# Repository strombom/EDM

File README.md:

# EDM

## Control board
* Stepper motor output.
* Power board control output.
* Buttons for stepper motor up/down and EDM start/stop.
* LCD display 4x20 characters for status.
* Potentiometers for setting voltage, current (not implemented in this revision), on-time and off-time.

## Power board
* Voltage source, low current for initiating spark. Selectable 250 V, 200 V, 150 V or 100 V. Status comparator checks if voltage is above 70 V.
* Current source, for providing current to the spark. Current limited to 10 A, adjustable with potentiometer.
Spark output, has two power transistors to enable the control board to control the voltage and current outputs independently. Has two comparators (5 V and 30 V) to give feedback to the control board, monitoring if a spark has started (breakdown) and to check for short circuit.

## Design files
* [Control Board Schematics](https://github.com/strombom/EDM/raw/master/hardware/edm_control_board/documents/edm_control_board_schematics.pdf)
* [Power Board Schematics](https://github.com/strombom/EDM/raw/master/hardware/edm_power_board/documents/edm_power_board_schematics.pdf)

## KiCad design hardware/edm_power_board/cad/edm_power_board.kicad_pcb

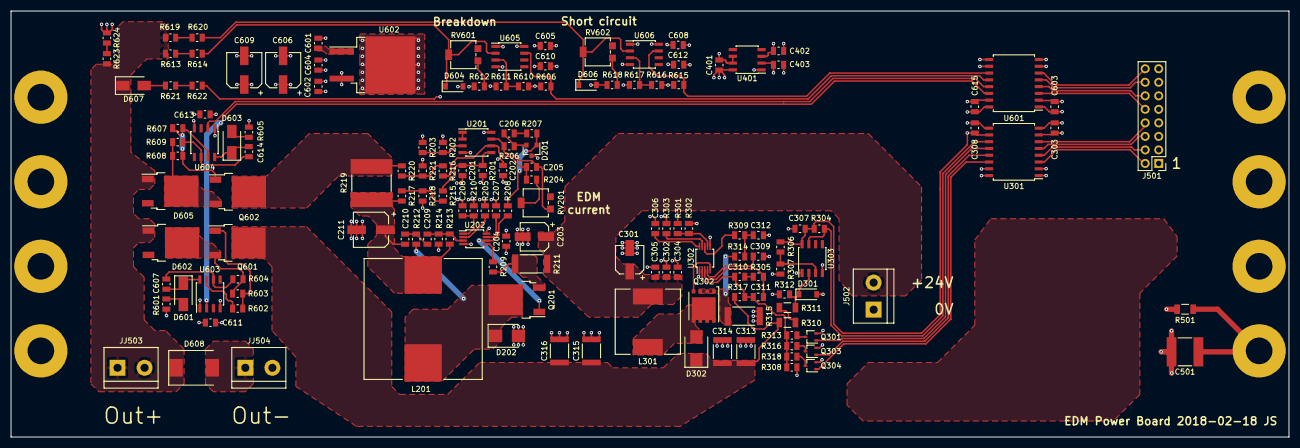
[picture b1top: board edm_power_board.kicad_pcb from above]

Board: 4 copper layers, 240.0 x 80.0 mm, 158 parts (0 on the bottom side), 89 nets.

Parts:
C201, C205: 220p; R_0805_2012Metric
C202, C204, C209, C303, C307, C308, C402, C602, C603, C605, C608, C610, C611, C612, C613, C615: 100n; C_0805_2012Metric
C203, C301: 22u; CP_Elec_5x5.3
C206, C306: 10n; C_0805_2012Metric
C207, C607, C614: 470n; C_0805_2012Metric
C208, C312: 1n; C_0805_2012Metric
C210: 3n3; C_0805_2012Metric
C211, C606, C609: 10u; CP_Elec_6.3x5.3
C302, C304, C305, C309, C403, C604: 1u; C_0805_2012Metric
C310: 120n; C_0805_2012Metric
C311: 560p; C_0805_2012Metric
C313, C314, C315, C316: 470n; C_1812_4532Metric
C401, C601: 330n; C_0805_2012Metric
C501: 1800p; C_2220_5650Metric
D201: TL431AIDBZR; SOT-23
D202, D302: S2JTR; D_SMB
D301, D604, D606: 4V7; D_SOD-123
D601, D603, D607: RS1MTR; D_SMA
D602, D605: VS-15EWL06FNTR-M3; TO-252-2
D608: 1.5SMC400CA; D_SMC
J501: Conn_02x08_Odd_Even; PinHeader_2x08_P2.54mm_Vertical
J502: Conn_01x02; TerminalBlock_bornier-2_P5.08mm
JJ503, JJ504: Conn_01x02; TerminalBlock_bornier-2_P5.08mm
L201: 6u8; L_Wuerth_HCI-2212
L301: 1m; L_Pulse_PA4320
MK501, MK502, MK503, MK504, MK507, MK508, MK509, MK510: Mounting_Hole_PAD; MountingHole_5mm_Pad
Q201: SUD19P06-60; TO-252-2
Q301, Q303, Q304: BSS214NW; SOT-323_SC-70
Q302: BSC13DN30NSFD; TDSON-8-1
Q601: IPD50R3K0CE; TO-252-2
Q602: IPD50R380CE; TO-252-2
R201, R202, R203, R207, R301, R306, R610, R616, R617: 27k; R_0805_2012Metric
R204, R208, R603, R608: 4k7; R_0805_2012Metric
R205: 243k; R_0805_2012Metric
R206: 10R; R_0805_2012Metric
R209: 100R; R_0805_2012Metric
R210: 6k34; R_0805_2012Metric
R211: 10m; R_2512_6332Metric
R212: 47k; R_0805_2012Metric
R213: 15k; R_0805_2012Metric
R214, R215, R216, R217, R218, R220, R221: 1k; R_0805_2012Metric
R219: 20m; R_Stackpole_CSSH2728_4-100m
R302: 2k2; R_0805_2012Metric
R303, R307, R611: 84k5; R_0805_2012Metric
R304, R606, R612, R615, R618, R621, R622: 21k; R_0805_2012Metric
R305: 3k; R_0805_2012Metric
R308, R316: 26k1; R_0805_2012Metric
R309: 10k5; R_0805_2012Metric
R310, R311: 93k1; R_1206_3216Metric
R312: 10k; R_0805_2012Metric
R313: 52k3; R_0805_2012Metric
R314: 102R; R_0805_2012Metric
R315: 150m; R_2512_6332Metric
R317: 2M1; R_0805_2012Metric
R318: 18k; R_0805_2012Metric
R501: 1M; R_1206_3216Metric
R601, R604, R605, R609: 4R99; R_0805_2012Metric
R602, R607: 47R; R_0805_2012Metric
R613, R614, R619, R620, R623, R624: 187k; R_0805_2012Metric
RV201: 50k; Potentiometer_Bourns_3314G_Horizontal
RV601: 100k; Potentiometer_Bourns_3314G_Horizontal
RV602: 500k; Potentiometer_Bourns_3314G_Horizontal
U201: LM358; SOIC-8_3.9x4.9mm_P1.27mm
U202: LM25085MM; MSOP-8_3x3mm_P0.65mm
U301: Si8641BB-B-IS; SOIC-16W_7.5x10.3mm_P1.27mm
U302: LM5022MM; MSOP-10_3x3mm_P0.5mm
U303, U605, U606: LM311; SOIC-8_3.9x4.9mm_P1.27mm
U401: L78L05_SO8; SOIC-8_3.9x4.9mm_P1.27mm
U601: Si8642BB-B-IS; SOIC-16W_7.5x10.3mm_P1.27mm
U602: L7815; TO-263-2
U603, U604: FAN7371; SOIC-8_3.9x4.9mm_P1.27mm

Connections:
+3V3: C303.1, C603.1, J501.1, U301.1, U301.7, U601.1, U601.7
+5V: C307.1, C308.1, C402.1, C403.1, C605.1, C608.1, C610.1, C612.1, C615.1, R304.1, R306.1, R606.2, R610.2, R615.2, R616.2, R622.2, U301.10, U301.16, U303.8, U401.1, U601.10, U601.16, U605.8, U606.8
+15V: C602.1, C604.1, C606.1, C609.1, C611.1, C613.1, R601.2, R605.2, U602.3, U603.1, U604.1
+24V: C202.1, C203.1, C204.1, C207.1, C208.1, C301.1, C302.1, C304.1, C305.1, C401.1, J502.2, L301.1, R202.1, R205.1, R210.1, R211.1, R301.1, U201.8, U202.8, U302.1, U401.8
/Connectors/Breakdown: J501.16, U601.6
/Connectors/Output_20V_Enable: J501.12, U601.4
/Connectors/Output_250V_Enable: J501.10, U601.3
/Connectors/Shield: C501.1, MK501.1, MK502.1, MK503.1, MK504.1, MK507.1, MK508.1, MK509.1, MK510.1, R501.1
/Connectors/Short_Circuit: J501.14, U601.5
/Connectors/Spark_Output: D602.1, D605.1, D607.1, D608.1, JJ503.1, JJ503.2, R613.2, R619.2, R623.2
/Connectors/Spark_Voltage_0: J501.2, U301.3
/Connectors/Spark_Voltage_1: J501.4, U301.4
/Connectors/Spark_Voltage_2: J501.6, U301.5
/Connectors/Spark_Voltage_Status: J501.8, U301.6
/Current Source/+20V: Q602.2, R219.1, R220.1
/Current Source/CS_1: C205.1, R206.2, RV201.3, U201.7
/Current Source/CS_1+: R216.1, R220.2, R221.1
/Current Source/CS_1-: R215.1, R217.2, R218.1
/Current Source/CS_2: C206.2, D201.2, R206.1
/Current Source/CS_2+: C205.2, R204.2, R216.2, U201.6
/Current Source/CS_2-: C201.1, R201.1, R215.2, U201.5
/Current Source/CS_3: C206.1, R207.2
/Current Source/CS_4: D201.1, R207.1, R208.2
/Current Source/CS_5: R204.1, RV201.2
/Current Source/CS_ADJ: C208.2, R210.2, U202.1
/Current Source/CS_FB: C209.2, R213.2, R214.1, U202.3
/Current Source/CS_ISEN: R209.2, U202.5
/Current Source/CS_NC1: R202.2, R203.1, U201.3
/Current Source/CS_NC2: U201.1, U201.2
/Current Source/CS_OUT: C210.1, C211.1, L201.2, R213.1, R217.1, R219.2
/Current Source/CS_PGATE: Q201.1, R208.1, U202.6
/Current Source/CS_QD: D202.1, L201.1, Q201.2, R212.2
/Current Source/CS_QD1: C209.1, C210.2, R212.1
/Current Source/CS_QS: Q201.3, R209.1, R211.2
/Current Source/CS_RT: R205.2, U202.2
/Current Source/CS_VCC: C207.2, U202.7
/Spark Output/+20V_Out: D605.2, Q602.3, R608.1, R609.1
/Spark Output/+24V: C601.1, U602.1
/Spark Output/+250V: C313.1, C314.1, C315.1, C316.1, D302.1, Q601.2, R310.1, R317.1
/Spark Output/+250V_Out: D602.2, Q601.3, R603.1, R604.1
/Spark Output/HV_ENA: R602.2, U603.7
/Spark Output/HV_ENB: Q601.1, R602.1, R603.2
/Spark Output/HV_VB: C607.1, D601.1, U603.8
/Spark Output/HV_VS: C607.2, R604.2, U603.6
/Spark Output/LV_ENA: R607.2, U604.7
/Spark Output/LV_ENB: Q602.1, R607.1, R608.2
/Spark Output/LV_VB: C614.1, D603.1, U604.8
/Spark Output/LV_VS: C614.2, R609.2, U604.6
/Spark Voltage Source/VS_COMP: C311.2, R305.2, U302.3
/Spark Voltage Source/VS_CS: R309.2, U302.8
/Spark Voltage Source/VS_CS2: C312.1, R309.1, R314.2
/Spark Voltage Source/VS_FB: C310.1, C311.1, R308.1, R313.1, R316.1, R317.2, R318.1, U302.2
/Spark Voltage Source/VS_OUT: Q302.4, U302.5
/Spark Voltage Source/VS_QD: D302.2, L301.2, Q302.5
/Spark Voltage Source/VS_QS: Q302.1, Q302.2, Q302.3, R314.1, R315.1
/Spark Voltage Source/VS_RT: R303.1, U302.9
/Spark Voltage Source/VS_UVLO: R301.2, R302.1, U302.7
/Spark Voltage Source/VS_VCC: C309.1, U302.4
GND: C303.2, C603.2, J501.3, J501.5, J501.7, J501.9, J501.11, J501.13, J501.15, U301.2, U301.8, U601.2, U601.8
GNDPWR: C201.2, C202.2, C203.2, C204.2, C211.2, C301.2, C302.2, C304.2, C305.2, C306.2, C307.2, C308.2, C309.2, C312.2, C313.2, C314.2, C315.2, C316.2, C401.2, C402.2, C403.2, C501.2, C601.2, C602.2, C604.2, C605.2, C606.2, C608.2, C609.2, C610.2, C611.2, C612.2, C613.2, C615.2, D201.3, D202.2, D301.2, D604.2, D606.2, D608.2, J502.1, JJ504.1, JJ504.2, Q301.2, Q303.2, Q304.2, R201.2, R203.2, R214.2, R218.2, R221.2, R302.2, R303.2, R307.2, R308.2, R312.2, R315.2, R501.2, R611.1, R612.1, R617.1, R618.1, R624.1, U201.4, U202.4, U301.9, U301.15, U302.6, U303.1, U303.4, U401.2, U401.3, U401.6, U401.7, U601.9, U601.15, U602.2, U603.4, U604.4, U605.1, U605.4, U606.1, U606.4
unnamed: C306.1, U302.10
unnamed: C310.2, R305.1
unnamed: D301.1, R311.2, R312.1, U303.2
unnamed: D601.2, R601.1
unnamed: D603.2, R605.1
unnamed: D604.1, R614.1, RV601.2, U605.2
unnamed: D606.1, R620.1, RV602.2, U606.2
unnamed: D607.2, R621.1
unnamed: Q301.1, U301.12
unnamed: Q301.3, R313.2
unnamed: Q303.1, U301.13
unnamed: Q303.3, R316.2
unnamed: Q304.1, U301.14
unnamed: Q304.3, R318.2
unnamed: R304.2, U301.11, U303.7
unnamed: R306.2, R307.1, U303.3
unnamed: R310.2, R311.1
unnamed: R606.1, U601.12, U605.7
unnamed: R610.1, R611.2, U605.3
unnamed: R612.2, RV601.3
unnamed: R613.1, R614.2
unnamed: R615.1, U601.11, U606.7
unnamed: R616.1, R617.2, U606.3
unnamed: R618.2, RV602.3
unnamed: R619.1, R620.2
unnamed: R621.2, R622.1
unnamed: R623.1, R624.2
unnamed: U601.13, U604.2
unnamed: U601.14, U603.2

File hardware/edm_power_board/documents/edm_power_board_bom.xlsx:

Ref | Qnty | Value | Digikey | Footprint
C201, C205 | 2 | 220p | 311-1115-1-ND | Resistor_SMD:R_0805_2012Metric
C203, C301 | 2 | 22u | PCE4240CT-ND | Capacitor_SMD:CP_Elec_5x5.3
C204, C209, C202, C308, C303, C307, C402, C603, C605, C608, C610, C612, C602, C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 | 16 | 100n | 445-1418-1-ND | Capacitor_SMD:C_0805_2012Metric
C206, C306 | 2 | 10n | 490-1664-1-ND | Capacitor_SMD:C_0805_2012Metric
C207, C607, C614 | 3 | 470n | 1276-1074-1-ND | Capacitor_SMD:C_0805_2012Metric
C208, C312 | 2 | 1n | 399-1147-1-ND | Capacitor_SMD:C_0805_2012Metric
C210 | 1 | 3n3 | 311-1131-1-ND | Capacitor_SMD:C_0805_2012Metric
C211, C606, C609 | 3 | 10u | PCE4209CT-ND | Capacitor_SMD:CP_Elec_6.3x5.3
C309, C305, C304, C302, C403, C604 | 6 | 1u | 587-2910-1-ND | Capacitor_SMD:C_0805_2012Metric
C310 | 1 | 120n | 1276-6518-1-ND | Capacitor_SMD:C_0805_2012Metric
C311 | 1 | 560p | 399-3492-1-ND | Capacitor_SMD:C_0805_2012Metric
C313, C314, C315, C316 | 4 | 470n | 445-13461-1-ND | Capacitor_SMD:C_1812_4532Metric
C401, C601 | 2 | 330n | 1276-6813-1-ND | Capacitor_SMD:C_0805_2012Metric
C501 | 1 | 1800p | 490-3479-1-ND | Capacitor_SMD:C_2220_5650Metric
D201 | 1 | TL431AIDBZR | 296-17329-1-ND | Package_TO_SOT_SMD:SOT-23
D202, D302 | 2 | S2JTR | 1655-1739-1-ND | Diode_SMD:D_SMB
D301, D604, D606 | 3 | 4V7 | BZT52C4V7-13FDICT-ND | Diode_SMD:D_SOD-123
D601, D603, D607 | 3 | RS1MTR | 1655-1501-1-ND | Diode_SMD:D_SMA
D602, D605 | 2 | VS-15EWL06FNTR-M3 | VS-15EWL06FNTR-M3CT-ND | Package_TO_SOT_SMD:TO-252-2
D608 | 1 | 1.5SMC400CA | 1.5SMC400CACT-ND | Diode_SMD:D_SMC
J501 | 1 | Conn_02x08_Odd_Even | ED10523-ND | Connector_PinHeader_2.54mm:PinHeader_2x08_P2.54mm_Vertical
J502, JJ503, JJ504 | 3 | Conn_01x02 | ED1609-ND | TerminalBlock:TerminalBlock_bornier-2_P5.08mm
L201 | 1 | 6u8 | 732-4233-1-ND | Inductor_SMD:L_Wuerth_HCI-2212
L301 | 1 | 1m | 553-3686-1-ND | Inductor_SMD:L_Pulse_PA4320
Q201 | 1 | SUD19P06-60 | SUD19P06-60-GE3CT-ND | Package_TO_SOT_SMD:TO-252-2
Q301, Q303, Q304 | 3 | BSS214NW | BSS214NWH6327XTSA1CT-ND | Package_TO_SOT_SMD:SOT-323_SC-70
Q302 | 1 | BSC13DN30NSFD | BSC13DN30NSFDATMA1CT-ND | Package_TO_SOT_SMD:TDSON-8-1
Q601 | 1 | IPD50R3K0CE | IPD50R3K0CEAUMA1CT-ND | Package_TO_SOT_SMD:TO-252-2
Q602 | 1 | IPD50R380CE | IPD50R380CEAUMA1CT-ND | Package_TO_SOT_SMD:TO-252-2
R201, R207, R202, R203, R301, R306, R610, R616, R617 | 9 | 27k | 311-27.0KCRCT-ND | Resistor_SMD:R_0805_2012Metric
R204, R208, R603, R608 | 4 | 4k7 | 311-4.70KCRCT-ND | Resistor_SMD:R_0805_2012Metric
R205 | 1 | 243k | YAG1838CT-ND | Resistor_SMD:R_0805_2012Metric
R206 | 1 | 10R | 311-10.0CRCT-ND | Resistor_SMD:R_0805_2012Metric
R209 | 1 | 100R | 311-100CRCT-ND | Resistor_SMD:R_0805_2012Metric
R210 | 1 | 6k34 | 311-6.34KCRCT-ND | Resistor_SMD:R_0805_2012Metric
R211 | 1 | 10m | CRA2512-FZ-R010ELFCT-ND | Resistor_SMD:R_2512_6332Metric
R212 | 1 | 47k | 311-47.0KCRCT-ND | Resistor_SMD:R_0805_2012Metric
R213 | 1 | 15k | 311-15.0KCRCT-ND | Resistor_SMD:R_0805_2012Metric
R214, R217, R220, R218, R221, R215, R216 | 7 | 1k | 311-1.00KCRCT-ND | Resistor_SMD:R_0805_2012Metric
R219 | 1 | 20m | CSSH2728FT20L0CT-ND | Resistor_SMD:R_Stackpole_CSSH2728_4-100m
R302 | 1 | 2k2 | 311-2.20KCRCT-ND | Resistor_SMD:R_0805_2012Metric
R304, R606, R612, R615, R618, R621, R622 | 7 | 21k | 311-21.0KCRCT-ND | Resistor_SMD:R_0805_2012Metric
R305 | 1 | 3k | 311-3.00KCRCT-ND | Resistor_SMD:R_0805_2012Metric
R307, R303, R611 | 3 | 84k5 | 311-84.5KCRCT-ND | Resistor_SMD:R_0805_2012Metric
R308, R316 | 2 | 26k1 | 311-26.1KCRCT-ND | Resistor_SMD:R_0805_2012Metric
R309 | 1 | 10k5 | 311-10.5KCRCT-ND | Resistor_SMD:R_0805_2012Metric
R311, R310 | 2 | 93k1 | 311-93.1KCRCT-ND | Resistor_SMD:R_1206_3216Metric
R312 | 1 | 10k | 311-10.0KCRCT-ND | Resistor_SMD:R_0805_2012Metric
R313 | 1 | 52k3 | 311-52.3KCRCT-ND | Resistor_SMD:R_0805_2012Metric
R314 | 1 | 102R | 311-102CRCT-ND | Resistor_SMD:R_0805_2012Metric
R315 | 1 | 150m | 311-0.15TCT-ND | Resistor_SMD:R_2512_6332Metric
R317 | 1 | 2M1 | 311-2.10MCRCT-ND | Resistor_SMD:R_0805_2012Metric
R318 | 1 | 18k | 311-18.0KCRCT-ND | Resistor_SMD:R_0805_2012Metric
R501 | 1 | 1M | 311-1.00MFRCT-ND | Resistor_SMD:R_1206_3216Metric
R601, R604, R605, R609 | 4 | 4R99 | 311-4.99CRCT-ND | Resistor_SMD:R_0805_2012Metric
R602, R607 | 2 | 47R | 311-47.0CRCT-ND | Resistor_SMD:R_0805_2012Metric
R613, R614, R619, R620, R623, R624 | 6 | 187k | 311-187KCRCT-ND | Resistor_SMD:R_0805_2012Metric
RV201 | 1 | 50k | 3314G-503ECT-ND | Potentiometer_SMD:Potentiometer_Bourns_3314G_Horizontal
RV601 | 1 | 100k | 3314G-104ECT-ND | Potentiometer_SMD:Potentiometer_Bourns_3314G_Horizontal
RV602 | 1 | 500k | 3314G-504ECT-ND | Potentiometer_SMD:Potentiometer_Bourns_3314G_Horizontal
U201 | 1 | LM358 | LM358F-GE2CT-ND | Package_SO:SOIC-8_3.9x4.9mm_P1.27mm
U202 | 1 | LM25085MM | LM25085MM/NOPBCT-ND | Package_SO:MSOP-8_3x3mm_P0.65mm
U301 | 1 | Si8641BB-B-IS | SI8641BB-B-IS-ND | Package_SO:SOIC-16W_7.5x10.3mm_P1.27mm
U302 | 1 | LM5022MM | LM5022MM/NOPBCT-ND | Package_SO:MSOP-10_3x3mm_P0.5mm
U303, U605, U606 | 3 | LM311 | LM311MX/NOPBCT-ND | Package_SO:SOIC-8_3.9x4.9mm_P1.27mm
U401 | 1 | L78L05_SO8 | 497-1182-1-ND | Package_SO:SOIC-8_3.9x4.9mm_P1.27mm
U601 | 1 | Si8642BB-B-IS | SI8642BB-B-IS-ND | Package_SO:SOIC-16W_7.5x10.3mm_P1.27mm
U602 | 1 | L7815 | 497-1179-1-ND | Package_TO_SOT_SMD:TO-263-2
U603, U604 | 2 | FAN7171 | FAN7171MX-F085FSCT-ND | Package_SO:SOIC-8_3.9x4.9mm_P1.27mm

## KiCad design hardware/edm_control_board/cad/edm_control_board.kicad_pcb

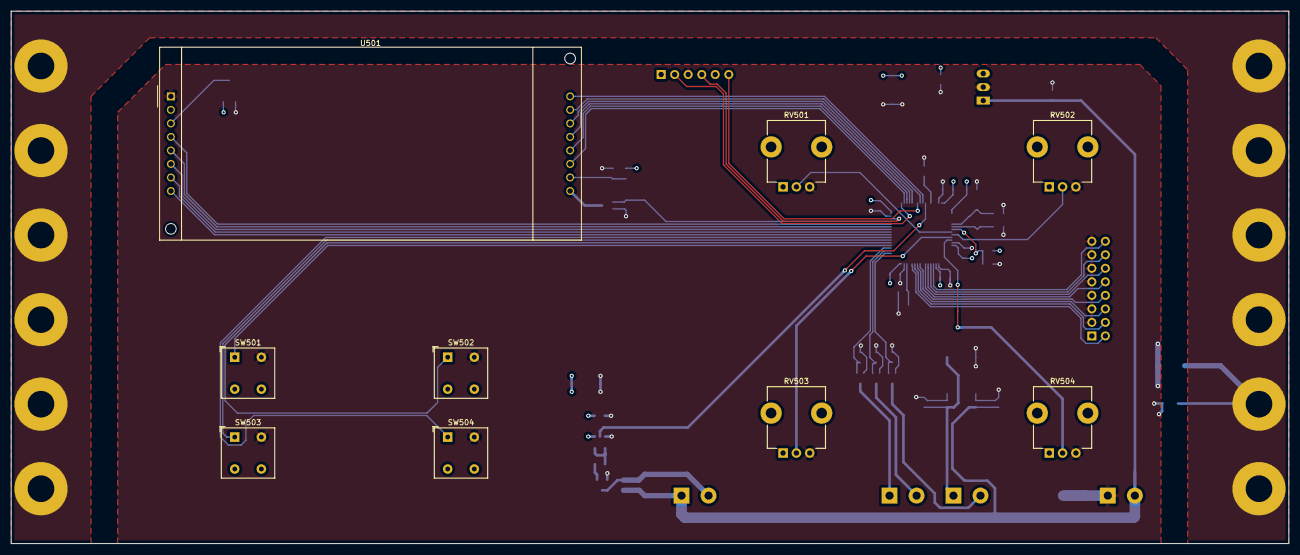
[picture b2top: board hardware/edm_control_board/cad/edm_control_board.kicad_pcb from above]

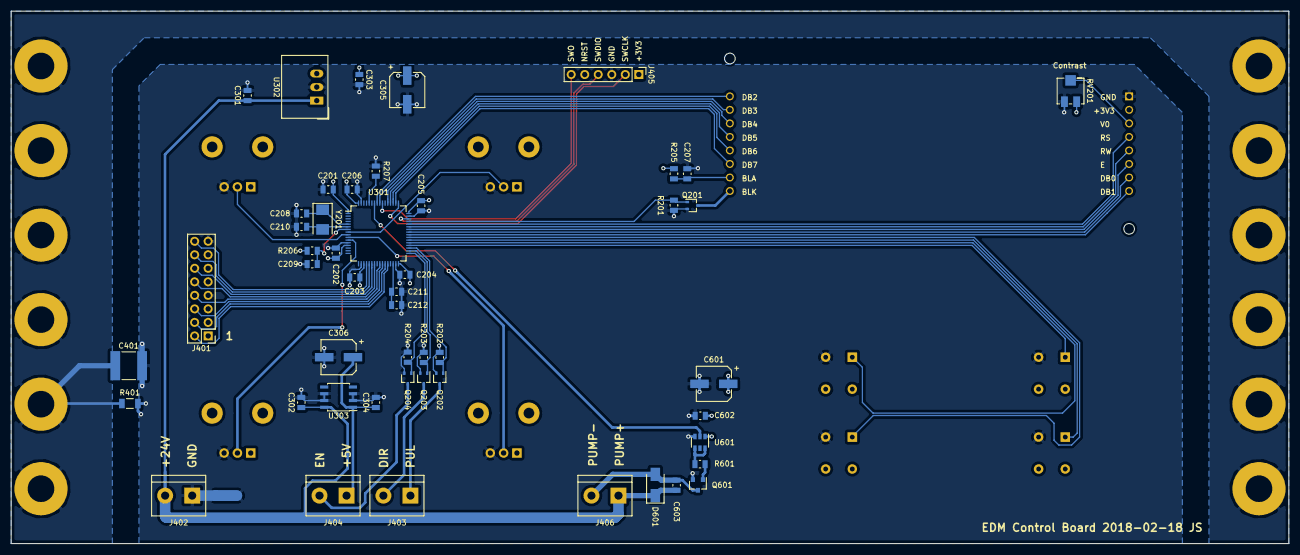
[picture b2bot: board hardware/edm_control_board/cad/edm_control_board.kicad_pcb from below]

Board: 4 copper layers, 240.0 x 100.0 mm, 71 parts (50 on the bottom side), 54 nets.

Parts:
C201, C202, C203, C204, C205, C206, C209, C303, C304, C602: 100n; C_0805_2012Metric
C207: 1u; C_0805_2012Metric
C208, C210: 12p; C_0805_2012Metric
C211, C212: 2u2; C_0805_2012Metric
C301, C302: 330n; C_0805_2012Metric
C305, C306, C601: 10u; CP_Elec_6.3x5.3
C401: 1800p; C_2220_5650Metric
C603: 1n; C_0805_2012Metric
D601: CDBA140-G; D_SMA
J401: Conn_02x08_Odd_Even; PinHeader_2x08_P2.54mm_Vertical
J402, J403, J404, J406: Conn_01x02; TerminalBlock_bornier-2_P5.08mm
J405: Conn_01x06; PinHeader_1x06_P2.54mm_Vertical
MK501, MK502, MK503, MK504, MK505, MK506, MK507, MK508, MK509, MK510, MK511, MK512: Mounting_Hole_PAD; MountingHole_5mm_Pad
NT301: Net-Tie_2; NetTie-2_SMD_Pad2.0mm
Q201, Q202, Q203, Q204: BSS214NW; SOT-323_SC-70
Q601: DMN3404L-7; SOT-23
R201, R202, R203, R204, R206, R207: 27k; R_0805_2012Metric
R205: 20R; R_0805_2012Metric
R401: 1M; R_1206_3216Metric
R601: 4R99; R_0805_2012Metric
RV201: 20k; Potentiometer_Bourns_3214J_Horizontal
RV501, RV502, RV503, RV504: POT; Potentiometer_TT_P0915N
SW501, SW502, SW503, SW504: SW_Push; SW_PUSH_CK_PVA1
U301: STM32F722RETx; LQFP-64_10x10mm_P0.5mm
U302: R-78E3.3-1.0; Converter_DCDC_RECOM_R-78E-0.5_THT
U303: L78L05_SO8; SOIC-8_3.9x4.9mm_P1.27mm
U501: NHD-0420H1Z
U601: ZXGD3009E6; SOT-23-6
Y201: 25M; Crystal_SMD_5032-2Pin_5.0x3.2mm

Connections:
+3V3: C201.1, C202.1, C203.1, C204.1, C205.1, C206.1, C303.1, C305.1, C601.1, C602.1, J401.1, J405.1, R205.2, R206.2, RV201.1, RV501.1, RV502.1, RV503.1, RV504.1, U301.1, U301.13, U301.19, U301.32, U301.48, U301.64, U302.3, U501.2, U601.1
+5V: C304.1, C306.1, J404.1, U303.1
+24V: C301.1, C302.1, C603.1, D601.1, J402.2, J406.1, U302.1, U303.8
/Connectors/Breakdown: J401.16, U301.20
/Connectors/Output_20V_Enable: J401.12, U301.22
/Connectors/Output_250V_Enable: J401.10, U301.23
/Connectors/SWCLK: J405.2, U301.49
/Connectors/SWDIO: J405.4, U301.46
/Connectors/SWO: J405.6, U301.55
/Connectors/Shield: C401.1, MK501.1, MK502.1, MK503.1, MK504.1, MK505.1, MK506.1, MK507.1, MK508.1, MK509.1, MK510.1, MK511.1, MK512.1, R401.1
/Connectors/Short_Circuit: J401.14, U301.21
/Connectors/Spark_Voltage_0: J401.2, U301.28
/Connectors/Spark_Voltage_1: J401.4, U301.27
/Connectors/Spark_Voltage_2: J401.6, U301.26
/Connectors/Spark_Voltage_Status: J401.8, U301.25
/Connectors/Stepper_DIR: J403.2, Q203.3
/Connectors/Stepper_EN: J404.2, Q204.3
/Connectors/Stepper_PUL: J403.1, Q202.3
/Connectors/Water_Pump_NEG: C603.2, D601.2, J406.2, Q601.3
/Controller/LCD_A: C207.1, R205.1, U501.15
/Controller/LCD_DB0: U301.41, U501.7
/Controller/LCD_DB1: U301.40, U501.8
/Controller/LCD_DB2: U301.57, U501.9
/Controller/LCD_DB3: U301.56, U501.10
/Controller/LCD_DB4: U301.53, U501.11
/Controller/LCD_DB5: U301.52, U501.12
/Controller/LCD_DB6: U301.51, U501.13
/Controller/LCD_DB7: U301.50, U501.14
/Controller/LCD_E: U301.42, U501.6
/Controller/LCD_K: Q201.3, U501.16
/Controller/LCD_RS: U301.44, U501.4
/Controller/LCD_RW: U301.43, U501.5
/Controller/LCD_V0: RV201.2, U501.3
/Controller/POT_1: RV501.2, U301.8
/Controller/POT_2: RV502.2, U301.9
/Controller/POT_3: RV503.2, U301.10
/Controller/POT_4: RV504.2, U301.11
/Controller/SW_1: SW501.1, U301.36
/Controller/SW_2: SW502.1, U301.37
/Controller/SW_3: SW503.1, U301.38
/Controller/SW_4: SW504.1, U301.39
/Controller/Water_Pump_PWM: U301.58, U601.2
GND: C201.2, C202.2, C203.2, C204.2, C205.2, C206.2, C207.2, C208.2, C209.2, C210.2, C211.2, C212.2, C301.2, C302.2, C303.2, C304.2, C305.2, C306.2, C401.2, C601.2, C602.2, J401.3, J401.5, J401.7, J401.9, J401.11, J401.13, J401.15, J402.1, J405.3, NT301.1, NT301.2, Q201.2, Q202.2, Q203.2, Q204.2, Q601.2, R201.2, R202.2, R203.2, R204.2, R207.2, R401.2, RV201.3, RV501.3, RV502.3, RV503.3, RV504.3, SW501.2, SW502.2, SW503.2, SW504.2, U301.12, U301.18, U301.31, U301.47, U301.63, U302.2, U303.2, U303.3, U303.6, U303.7, U501.1, U601.3
unnamed: C208.1, U301.5, Y201.1
unnamed: C209.1, R206.1, U301.7
unnamed: C210.1, U301.6, Y201.2
unnamed: C211.1, C212.1, U301.30
unnamed: Q201.1, R201.1, U301.45
unnamed: Q202.1, R202.1, U301.35
unnamed: Q203.1, R203.1, U301.34
unnamed: Q204.1, R204.1, U301.33
unnamed: Q601.1, R601.1
unnamed: R207.1, U301.60
unnamed: R601.2, U601.4, U601.6

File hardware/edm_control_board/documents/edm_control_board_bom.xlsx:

Ref | Qnty | Value | Digikey | Footprint
C201, C202, C203, C204, C205, C209, C206, C303, C304, C602 | 10 | 100n | 445-1418-1-ND | Capacitor_SMD:C_0805_2012Metric
C207 | 1 | 1u | 587-2910-1-ND | Capacitor_SMD:C_0805_2012Metric
C210, C208 | 2 | 12p | 311-1100-1-ND | Capacitor_SMD:C_0805_2012Metric
C212, C211 | 2 | 2u2 | 311-3425-1-ND | Capacitor_SMD:C_0805_2012Metric
C301, C302 | 2 | 330n | 1276-6813-1-ND | Capacitor_SMD:C_0805_2012Metric
C305, C306, C601 | 3 | 10u | PCE4209CT-ND | Capacitor_SMD:CP_Elec_6.3x5.3
C401 | 1 | 1800p | 490-3479-1-ND | Capacitor_SMD:C_2220_5650Metric
C603 | 1 | 1n | 311-1469-1-ND | Capacitor_SMD:C_0805_2012Metric
D601 | 1 | CDBA140-G | 641-1015-1-ND | Diode_SMD:D_SMA
J401 | 1 | Conn_02x08_Odd_Even | ED10523-ND | Connector_PinHeader_2.54mm:PinHeader_2x08_P2.54mm_Vertical
J402, J404, J403, J406 | 4 | Conn_01x02 | ED1609-ND | TerminalBlock:TerminalBlock_bornier-2_P5.08mm
J405 | 1 | Conn_01x06 | 952-2270-ND | Connector_PinHeader_2.54mm:PinHeader_1x06_P2.54mm_Vertical
Q202, Q203, Q204, Q201 | 4 | BSS214NW | BSS214NWH6327XTSA1 | Package_TO_SOT_SMD:SOT-323_SC-70
Q601 | 1 | DMN3404L-7 | DMN3404LDICT-ND | Package_TO_SOT_SMD:SOT-23
R202, R203, R204, R201, R207, R206 | 6 | 27k | 311-27.0KCRCT-ND | Resistor_SMD:R_0805_2012Metric
R205 | 1 | 20R | 311-20.0CRCT-ND | Resistor_SMD:R_0805_2012Metric
R401 | 1 | 1M | 311-1.00MFRCT-ND | Resistor_SMD:R_1206_3216Metric
R601 | 1 | 4R99 | 311-4.99CRCT-ND | Resistor_SMD:R_0805_2012Metric
RV201 | 1 | 20k | 3214J-203ECT-ND | Potentiometer_SMD:Potentiometer_Bourns_3214J_Horizontal
RV501, RV503, RV502, RV504 | 4 | POT | 987-1278-ND | Potentiometer_THT:Potentiometer_TT_P0915N
SW501, SW503, SW502, SW504 | 4 | SW_Push | 401-1137-ND | Button_Switch_THT:SW_PUSH_CK_PVA1
U301 | 1 | STM32F722RETx | 497-17184-ND | Package_QFP:LQFP-64_10x10mm_P0.5mm
U302 | 1 | R-78E3.3-1.0 | 945-2409-5-ND | Converter_DCDC:Converter_DCDC_RECOM_R-78E-0.5_THT
U303 | 1 | L78L05_SO8 | 497-1182-1-ND | Package_SO:SOIC-8_3.9x4.9mm_P1.27mm
U501 | 1 | NHD-0420H1Z | NHD-0420H1Z-FSW-GBW-33V3-ND | Display:NHD-0420H1Z
U601 | 1 | ZXGD3009E6 | ZXGD3009E6TADICT-ND | Package_TO_SOT_SMD:SOT-23-6
Y201 | 1 | 25M | 644-1041-1-ND | Crystal:Crystal_SMD_5032-2Pin_5.0x3.2mm

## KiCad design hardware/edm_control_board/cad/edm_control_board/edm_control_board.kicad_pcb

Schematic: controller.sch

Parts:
C201, C202, C203, C204, C205, C206, C209: 100n; C_0805_2012Metric; Digikey 445-1418-1-ND
C207: 1u; C_0805_2012Metric; Digikey 587-2910-1-ND
C208, C210: 12p; C_0805_2012Metric; Digikey 311-1641-1-ND
C211, C212: 2u2; C_0805_2012Metric; Digikey 311-1442-1-ND
Q201, Q202, Q203, Q204: BSS214NW; SOT-323_SC-70; Digikey BSS214NWH6327XTSA1
R201, R202, R203, R204, R206, R207: 27k; R_0805_2012Metric; Digikey 311-27.0KCRCT-ND
R205: 20R; R_0805_2012Metric; Digikey 311-20.0CRCT-ND
RV201: 20k; Potentiometer_Bourns_3214X_Vertical; Digikey 3214X-1-203ECT-ND
U301: STM32F722RETx; LQFP-64_10x10mm_P0.5mm
Y201: 25M; Crystal_SMD_5032-2Pin_5.0x3.2mm; Digikey 644-1041-1-ND

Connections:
+3V3: C201.1, C202.1, C203.1, C204.1, C205.1, C206.1, R205.2, R206.2, RV201.1, U301.1 (VBAT), U301.13 (VREF+), U301.19 (VDD), U301.32 (VDD), U301.48 (VDD), U301.64 (VDD); also elsewhere on the board
/Connectors/Breakdown: U301.59 (PB7); also elsewhere on the board
/Connectors/Output_20V_Enable: U301.57 (PB5); also elsewhere on the board
/Connectors/Output_250V_Enable: U301.56 (PB4); also elsewhere on the board
/Connectors/Short_Circuit: U301.58 (PB6); also elsewhere on the board
/Connectors/Spark_Voltage_0: U301.25 (PB0); also elsewhere on the board
/Connectors/Spark_Voltage_1: U301.26 (PB1); also elsewhere on the board
/Connectors/Spark_Voltage_2: U301.27 (PB2); also elsewhere on the board
/Connectors/Spark_Voltage_Status: U301.55 (PB3); also elsewhere on the board
/Connectors/Stepper_DIR: Q203.3; also elsewhere on the board
/Connectors/Stepper_EN: Q204.3; also elsewhere on the board
/Connectors/Stepper_PUL: Q202.3; also elsewhere on the board
/Controller/LCD_A: C207.1, R205.1; also elsewhere on the board
/Controller/LCD_DB0: U301.14 (PA0); also elsewhere on the board
/Controller/LCD_DB1: U301.15 (PA1); also elsewhere on the board
/Controller/LCD_DB2: U301.16 (PA2); also elsewhere on the board
/Controller/LCD_DB3: U301.17 (PA3); also elsewhere on the board
/Controller/LCD_DB4: U301.20 (PA4); also elsewhere on the board
/Controller/LCD_DB5: U301.21 (PA5); also elsewhere on the board
/Controller/LCD_DB6: U301.22 (PA6); also elsewhere on the board
/Controller/LCD_DB7: U301.23 (PA7); also elsewhere on the board
/Controller/LCD_E: U301.43 (PA10); also elsewhere on the board
/Controller/LCD_K: Q201.3; also elsewhere on the board
/Controller/LCD_RS: U301.41 (PA8); also elsewhere on the board
/Controller/LCD_RW: U301.42 (PA9); also elsewhere on the board
/Controller/LCD_V0: RV201.2; also elsewhere on the board
GND: C201.2, C202.2, C203.2, C204.2, C205.2, C206.2, C207.2, C208.2, C209.2, C210.2, C211.2, C212.2, Q201.2, Q202.2, Q203.2, Q204.2, R201.2, R202.2, R203.2, R204.2, R207.2, RV201.3, U301.12 (VSSA), U301.18 (VSS), U301.31 (VSS), U301.47 (VSS), U301.63 (VSS); also elsewhere on the board
unnamed: C208.1, U301.5 (PH0), Y201.1
unnamed: C209.1, R206.1, U301.7 (NRST)
unnamed: C210.1, U301.6 (PH1), Y201.2
unnamed: C211.1, C212.1, U301.30 (VCAP_1)
unnamed: Q201.1, R201.1, U301.50 (PA15)
unnamed: Q202.1, R202.1, U301.45 (PA12)
unnamed: Q203.1, R203.1, U301.46 (PA13)
unnamed: Q204.1, R204.1, U301.49 (PA14)
unnamed: R207.1, U301.60 (BOOT0)

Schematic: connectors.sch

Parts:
J501: Conn_02x08_Odd_Even; PinHeader_2x08_P2.54mm_Vertical; Digikey ED10523-ND
J502: Conn_01x02; TerminalBlock_bornier-2_P5.08mm; Digikey ED1609-ND
JJ503, JJ504: Conn_01x02; TerminalBlock_bornier-2_P5.08mm; Digikey ED1609-ND
MK501, MK502, MK503, MK504, MK505, MK506, MK507, MK508, MK509, MK510, MK511, MK512: Mounting_Hole_PAD; MountingHole_5mm_Pad

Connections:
+5V: JJ504.1; also elsewhere on the board
+24V: J502.2; also elsewhere on the board
/Connectors/+3V3: J501.1
/Connectors/Breakdown: J501.16; also elsewhere on the board
/Connectors/GND: J501.3, J501.5, J501.7, J501.9, J501.11, J501.13, J501.15
/Connectors/Output_20V_Enable: J501.12; also elsewhere on the board
/Connectors/Output_250V_Enable: J501.10; also elsewhere on the board
/Connectors/Short_Circuit: J501.14; also elsewhere on the board
/Connectors/Spark_Voltage_0: J501.2; also elsewhere on the board
/Connectors/Spark_Voltage_1: J501.4; also elsewhere on the board
/Connectors/Spark_Voltage_2: J501.6; also elsewhere on the board
/Connectors/Spark_Voltage_Status: J501.8; also elsewhere on the board
/Connectors/Stepper_DIR: JJ503.2; also elsewhere on the board
/Connectors/Stepper_EN: JJ504.2; also elsewhere on the board
/Connectors/Stepper_PUL: JJ503.1; also elsewhere on the board
GND: J502.1, MK501.1, MK502.1, MK503.1, MK504.1, MK505.1, MK506.1, MK507.1, MK508.1, MK509.1, MK510.1, MK511.1, MK512.1; also elsewhere on the board

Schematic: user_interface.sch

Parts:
RV401, RV402, RV403, RV404: POT; Potentiometer_TT_P0915N
SW401, SW402, SW403, SW404: SW_Push; SW_PUSH_CK_PVA1
U401: NHD-0420H1Z

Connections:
+3V3: RV401.1, RV402.1, RV403.1, RV404.1, U401.2; also elsewhere on the board
/Controller/LCD_A: U401.15; also elsewhere on the board
/Controller/LCD_DB0: U401.7; also elsewhere on the board
/Controller/LCD_DB1: U401.8; also elsewhere on the board
/Controller/LCD_DB2: U401.9; also elsewhere on the board
/Controller/LCD_DB3: U401.10; also elsewhere on the board
/Controller/LCD_DB4: U401.11; also elsewhere on the board
/Controller/LCD_DB5: U401.12; also elsewhere on the board
/Controller/LCD_DB6: U401.13; also elsewhere on the board
/Controller/LCD_DB7: U401.14; also elsewhere on the board
/Controller/LCD_E: U401.6; also elsewhere on the board
/Controller/LCD_K: U401.16; also elsewhere on the board
/Controller/LCD_RS: U401.4; also elsewhere on the board
/Controller/LCD_RW: U401.5; also elsewhere on the board
/Controller/LCD_V0: U401.3; also elsewhere on the board
/User Interface/POT_1: RV401.2
/User Interface/POT_2: RV402.2
/User Interface/POT_3: RV403.2
/User Interface/POT_4: RV404.2
/User Interface/SW_1: SW401.1
/User Interface/SW_2: SW402.1
/User Interface/SW_3: SW403.1
/User Interface/SW_4: SW404.1
GND: RV401.3, RV402.3, RV403.3, RV404.3, SW401.2, SW402.2, SW403.2, SW404.2, U401.1; also elsewhere on the board

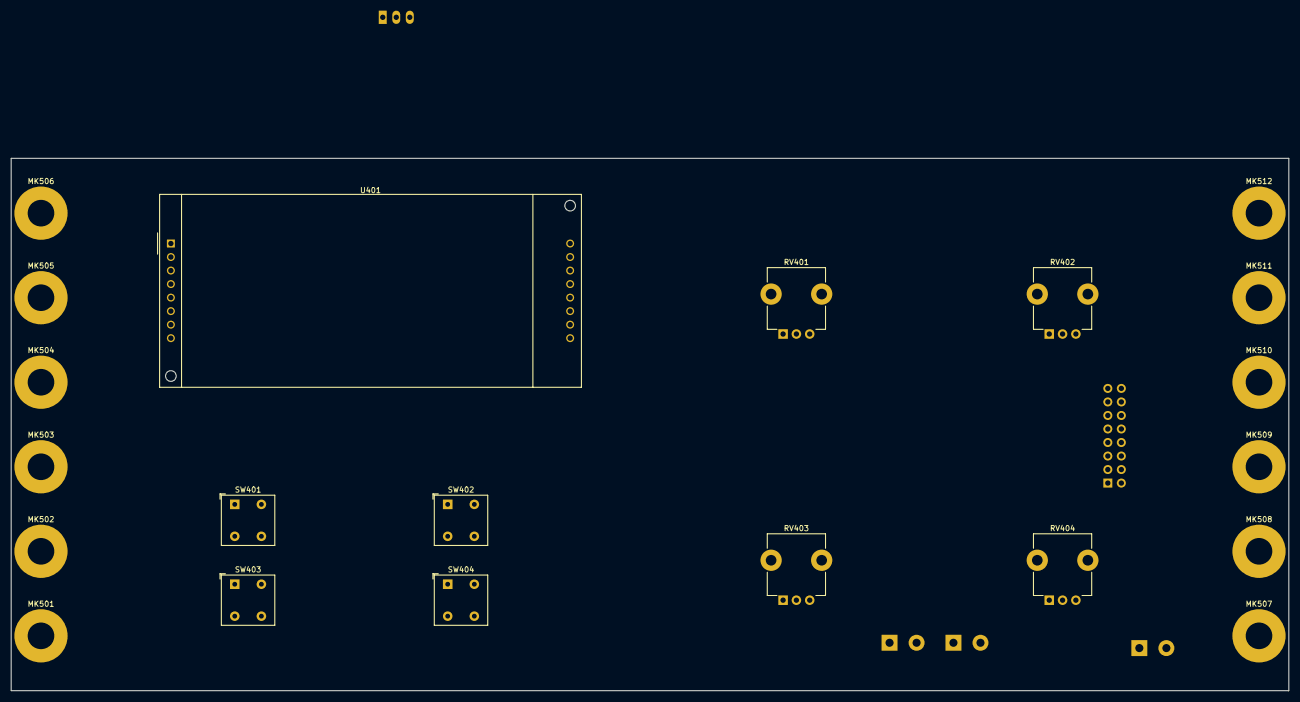
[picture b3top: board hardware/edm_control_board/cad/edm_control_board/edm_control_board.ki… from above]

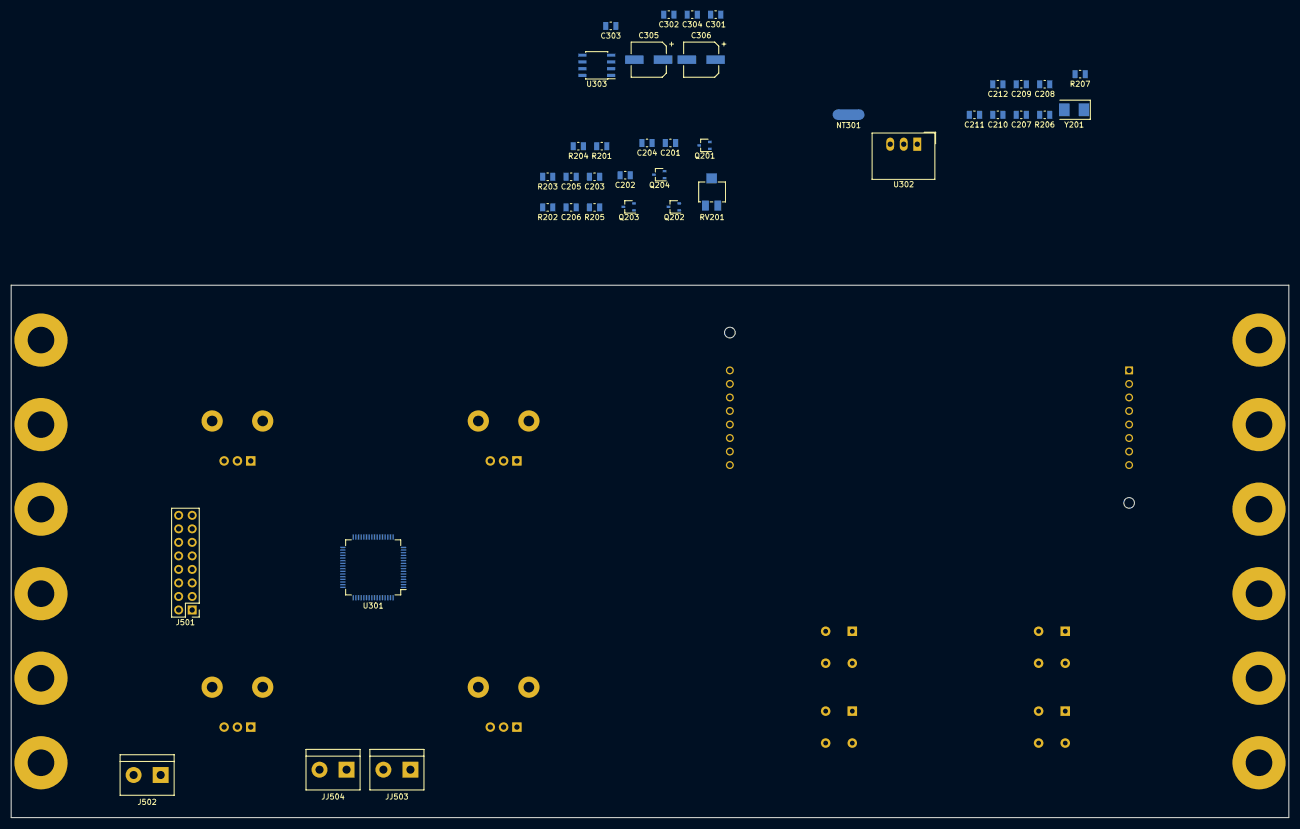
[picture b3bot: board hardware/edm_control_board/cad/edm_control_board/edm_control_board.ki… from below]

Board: 2 copper layers, 240.0 x 100.0 mm, 60 parts (39 on the bottom side), 39 nets, no tracks yet.

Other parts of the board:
C301, C302: 330n; C_0805_2012Metric
C303, C304: 100n; C_0805_2012Metric
C305, C306: 10u; CP_Elec_6.3x5.3
NT301: Net-Tie_2; NetTie-2_SMD_Pad2.0mm
U302: R-78E3.3-1.0; Converter_DCDC_RECOM_R-78E-0.5_THT
U303: L78L05_SO8; SOIC-8_3.9x4.9mm_P1.27mm

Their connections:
+3V3: C303.1, C305.1, U302.3; also elsewhere on the board
+5V: C304.1, C306.1, U303.1; also elsewhere on the board
+24V: C301.1, C302.1, U302.1, U303.8; also elsewhere on the board
GND: C301.2, C302.2, C303.2, C304.2, C305.2, C306.2, NT301.1, NT301.2, U302.2, U303.2, U303.3, U303.6, U303.7; also elsewhere on the board

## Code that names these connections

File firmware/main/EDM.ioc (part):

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Mcu.Name=STM32F722R(C-E)Tx
Mcu.Package=LQFP64
Mcu.UserName=STM32F722RCTx
PA10.GPIOParameters=GPIO_Label
PA10.GPIO_Label=LCD_RW
PA10.Signal=GPIO_Output
PA11.GPIOParameters=GPIO_Label
PA11.GPIO_Label=LCD_RS
PA11.Signal=GPIO_Output
PA12.GPIOParameters=GPIO_Label
PA12.GPIO_Label=LCD_Background_Illumination
PA12.Signal=GPIO_Output
PA13.Mode=Serial_Wire
PA13.Signal=SYS_JTMS-SWDIO
PA14.Mode=Serial_Wire
PA14.Signal=SYS_JTCK-SWCLK
PA15.GPIOParameters=GPIO_Label
PA15.GPIO_Label=LCD_DB7
PA15.Signal=GPIO_Output
PA4.GPIOParameters=GPIO_PuPd,GPIO_Label
PA4.GPIO_Label=EDM_Short_Circuit
PA4.GPIO_PuPd=GPIO_PULLDOWN
PA4.Signal=GPIO_Input
PA5.GPIOParameters=GPIO_PuPd,GPIO_Label
PA5.GPIO_Label=EDM_Breakdown
PA5.GPIO_PuPd=GPIO_PULLDOWN
PA5.Signal=GPIO_Input
PA6.GPIOParameters=GPIO_Label
PA6.GPIO_Label=EDM_Output_20V_Enable
PA6.Signal=GPIO_Output
PA7.GPIOParameters=GPIO_Label
PA7.GPIO_Label=EDM_Output_250V_Enable
PA7.Signal=GPIO_Output
PA8.GPIOParameters=GPIO_Label
PA8.GPIO_Label=LCD_DB0
PA8.Signal=GPIO_Output
PA9.GPIOParameters=GPIO_Label
PA9.GPIO_Label=LCD_E
PA9.Signal=GPIO_Output
PB0.GPIOParameters=GPIO_PuPd,GPIO_Label
PB0.GPIO_Label=EDM_Spark_Voltage_Status
PB0.GPIO_PuPd=GPIO_PULLDOWN
PB0.Signal=GPIO_Input
PB1.GPIOParameters=GPIO_Label
PB1.GPIO_Label=EDM_Spark_Voltage_2
PB1.Signal=GPIO_Output
PB10.GPIOParameters=GPIO_Label
PB10.GPIO_Label=EDM_Spark_Voltage_0
PB10.Signal=GPIO_Output
PB12.GPIOParameters=PinState,GPIO_Label
PB12.GPIO_Label=Stepper_EN
PB12.PinState=GPIO_PIN_SET
PB12.Signal=GPIO_Output
PB13.GPIOParameters=GPIO_Label
PB13.GPIO_Label=Stepper_DIR
PB13.Signal=GPIO_Output
PB14.GPIOParameters=GPIO_Label
PB14.GPIO_Label=Stepper_PUL
PB14.Signal=S_TIM12_CH1
PB15.GPIOParameters=GPIO_PuPd,GPIO_Label
PB15.GPIO_Label=Button_1
PB15.GPIO_PuPd=GPIO_PULLUP
PB15.Signal=GPIO_Input
PB2.GPIOParameters=GPIO_Label
PB2.GPIO_Label=EDM_Spark_Voltage_1
PB2.Signal=GPIO_Output
PB4.GPIOParameters=GPIO_Label
PB4.GPIO_Label=LCD_DB3
PB4.Signal=GPIO_Output
PB5.GPIOParameters=GPIO_Label
PB5.GPIO_Label=LCD_DB2
PB5.Signal=GPIO_Output
PB6.GPIOParameters=GPIO_Label
PB6.GPIO_Label=Water_Pump_PWM
PB6.Signal=S_TIM4_CH1
PC0.GPIOParameters=GPIO_Label
PC0.GPIO_Label=POT_1
PC0.Signal=ADCx_IN10
PC1.GPIOParameters=GPIO_Label
PC1.GPIO_Label=POT_2
PC1.Signal=ADCx_IN11
PC10.GPIOParameters=GPIO_Label
PC10.GPIO_Label=LCD_DB6
PC10.Signal=GPIO_Output
PC11.GPIOParameters=GPIO_Label
PC11.GPIO_Label=LCD_DB5
PC11.Signal=GPIO_Output
PC12.GPIOParameters=GPIO_Label
PC12.GPIO_Label=LCD_DB4
PC12.Signal=GPIO_Output
PC2.GPIOParameters=GPIO_Label
PC2.GPIO_Label=POT_3
PC2.Signal=ADCx_IN12
PC3.GPIOParameters=GPIO_Label
PC3.GPIO_Label=POT_4
PC3.Signal=ADCx_IN13
PC6.GPIOParameters=GPIO_PuPd,GPIO_Label
PC6.GPIO_Label=Button_2
PC6.GPIO_PuPd=GPIO_PULLUP
PC6.Signal=GPIO_Input
PC7.GPIOParameters=GPIO_PuPd,GPIO_Label
PC7.GPIO_Label=Button_3
PC7.GPIO_PuPd=GPIO_PULLUP
PC7.Signal=GPIO_Input
PC8.GPIOParameters=GPIO_PuPd,GPIO_Label
PC8.GPIO_Label=Button_4
PC8.GPIO_PuPd=GPIO_PULLUP
PC8.Signal=GPIO_Input
PC9.GPIOParameters=GPIO_Label
PC9.GPIO_Label=LCD_DB1
PC9.Signal=GPIO_Output
PH0-OSC_IN.Mode=HSE-External-Oscillator
PH0-OSC_IN.Signal=RCC_OSC_IN
PH1-OSC_OUT.Mode=HSE-External-Oscillator
PH1-OSC_OUT.Signal=RCC_OSC_OUT
RCC.HSE_VALUE=25000000
RCC.SYSCLKFreq_VALUE=216000000
RCC.SYSCLKSource=RCC_SYSCLKSOURCE_PLLCLK
board=EDM

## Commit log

2018-01-31 KiCAD project
2018-01-31 Low voltage source
2018-01-31 Current source
2018-02-01 Spark voltage source
2018-02-01 Remove bak file
2018-02-05 Insulator
2018-02-06 Spark output
2018-02-07 Interconnections
2018-02-08 Assign part numbers
2018-02-08 Set component references
2018-02-10 Set part numbers
2018-02-11 PCB Outline
2018-02-11 Add input capacitors to spark
2018-02-11 Component placement 250V
2018-02-11 Spark output connector
2018-02-11 Plated mounting holes
2018-02-12 Component placement
2018-02-12 Add 3D cad
2018-02-13 Routing
2018-02-13 Move files
2018-02-13 Add bleeder resistor, remove 25u capacitors
2018-02-13 Update bleed resistor
2018-02-16 Rotate board
2018-02-16 Control board
2018-02-17 Main sheet
2018-02-17 Power supply
2018-02-17 Microcontroller
2018-02-17 Change folder
2018-02-17 Change to horizontal trim pot
2018-02-17 Update pinout
2018-02-18 Add SWD connector
2018-02-18 Add Y capacitor
2018-02-18 3D files
2018-02-18 Add pdf schematics
2018-02-19 Add water pump output
2018-02-19 Add water pump to pcb
2018-02-19 Added copper planes to front and back. Added gerber files.
2018-02-20 Add BOM
2018-02-25 EDM Machine 3D CAD
2018-02-25 EDM Control Box 3D CAD
2018-02-25 Add screw M3 12mm
2018-02-25 Remove old files
2018-02-27 Mechanics
2018-02-27 Firmware project
2018-02-27 Add PIN functions
2018-02-27 Stepper pulse output description
2018-02-28 Generate firmware project with STM32CubeMX
2018-02-28 Update slide holder
2018-03-01 Oil filter holder in progress
2018-03-01 Oil filter holder update
2018-03-01 Remove temporary file
2018-03-03 Display
2018-03-06 Change C211, C212 from 0402 to 0805
2018-03-06 Change C208, C210 from 0402 to 0805
2018-03-07 Add NRST to SWD connector
2018-03-07 Display works
2018-03-07 Update schematics with new STM32 symbol
2018-03-07 Print menu
2018-03-07 Add EdmState, Change indentations to spaces
2018-03-07 Remove comments
2018-03-07 Time and voltage settings
2018-03-08 WaterPump class
2018-03-08 Change terminal name from GND to +5V
2018-03-09 Stepper motor control
2018-03-09 Control spark voltage
2018-03-09 Breakdown and Short circuit pins
2018-03-10 Breakdown and short circuit pins mixed
2018-03-10 Power board control
2018-03-12 Update CubeMX script, update indentation, add timer 9
2018-03-12 TIM9 init, restore TIM12 prescaler
2018-03-12 Tim9 as us delay, add printf
2018-03-13 Ton toff float to int
2018-03-13 PCB Errata
2018-03-13 Spark control
2018-03-21 EdmState logic
2018-03-21 Retract, water pump
